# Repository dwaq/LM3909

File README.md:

# LM3909
A clone of National Semiconductor's LM3909 IC using discrete components on a PCB.

Project page: [https://hackaday.io/project/29179-disintegrated-lm3909-15v-led-flasher](https://hackaday.io/project/29179-disintegrated-lm3909-15v-led-flasher)

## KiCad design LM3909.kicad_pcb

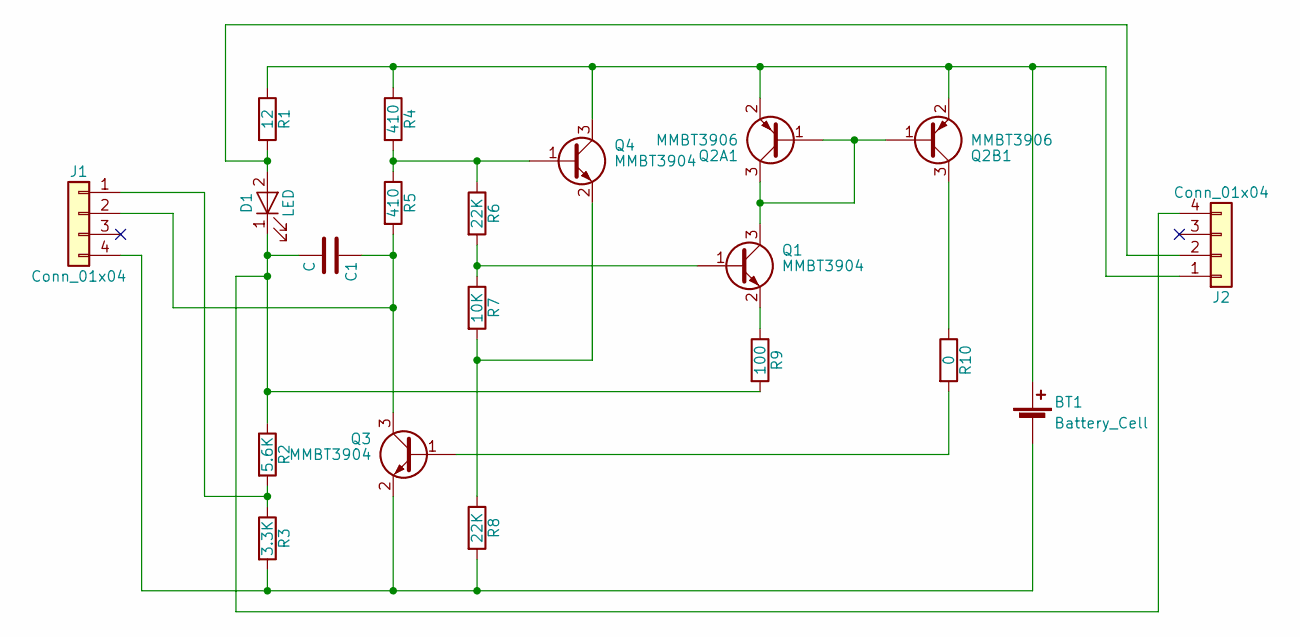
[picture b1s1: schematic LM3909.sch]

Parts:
BT1: Battery_Cell
C1: C; C_1206
D1: LED; LED_0805
J1, J2: Conn_01x04; Pin_Header_Straight_1x04_Pitch2.54mm
Q1, Q3, Q4: MMBT3904; SOT-23
Q2A1, Q2B1: MMBT3906; SOT-23
R1: 12; R_0805
R2: 5.6K; R_0805
R3: 3.3K; R_0805
R4, R5: 410; R_0805
R6, R8: 22K; R_0805
R7: 10K; R_0805
R9: 100; R_0805
R10: 0; R_0805

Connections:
unnamed 0: BT1.1 (+), J2.1, Q2A1.2 (E), Q2B1.2 (E), Q4.3 (C), R1.1, R4.1; also elsewhere on the board
unnamed: BT1.2 (-), J1.4, Q3.2 (E), R3.2, R8.2
unnamed: C1.1, J1.2, Q3.3 (C), R5.2
unnamed: C1.2, D1.1 (K), J2.4, R2.1, R9.2
unnamed: D1.2 (A), J2.2, R1.2
unnamed: J1.1, R2.2, R3.1
unnamed: Q1.1 (B), R6.2, R7.1
unnamed: Q1.2 (E), R9.1
unnamed 10: Q1.3 (C), Q2A1.1 (B), Q2A1.3 (C), Q2B1.1 (B); also elsewhere on the board
unnamed: Q2B1.3 (C), R10.1
unnamed: Q3.1 (B), R10.2
unnamed: Q4.1 (B), R4.2, R5.1, R6.1
unnamed: Q4.2 (E), R7.2, R8.1

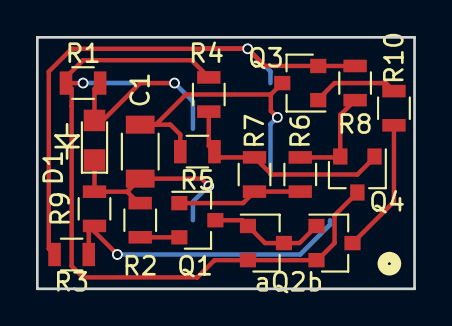
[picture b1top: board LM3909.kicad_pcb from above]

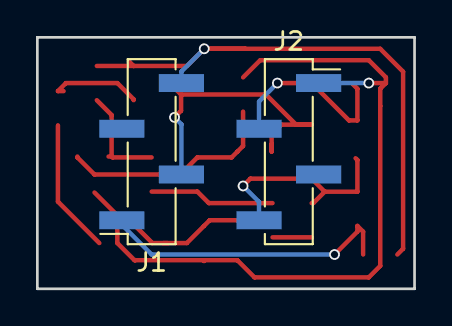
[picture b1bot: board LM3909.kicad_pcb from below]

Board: 2 copper layers, 21.0 x 14.0 mm, 19 parts (2 on the bottom side), 13 nets.

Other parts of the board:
aQ2b: MMBT3906; SOT-23

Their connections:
unnamed 0: aQ2b.2; also elsewhere on the board
unnamed 10: aQ2b.1, aQ2b.3; also elsewhere on the board

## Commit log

2017-11-29 init kicad project
2017-11-29 add gitignore
2017-11-29 connect all components in schematic
2017-11-29 add values
2017-11-29 add reference designators
2017-11-29 add 0805 footprints to many components
2017-11-29 generate netlist
    and automatically rename Q2x to Q2x1
2017-11-29 ignore other files
2017-11-29 place components on PCB
2017-11-29 start to lay traces
2017-11-30 replace through hole transistors with smd parts
2017-11-30 add another R that can be used intead of transistor current mirror
2017-11-30 route some more
2017-12-01 connected everything on one layer
2017-12-01 condensed
2017-12-01 much smaller
2017-12-01 loop wires other way
2017-12-01 pretty dang small
2017-12-01 condense schematic
2017-12-01 add pins to schematic
2017-12-01 add through hole pin footprint
2017-12-03 new footprint
    switched to offset smd
    in correct position to match DIP
2017-12-04 replace BC8*7 with MMBT390* transistors
2017-12-04 hide text on board
    Visables -> Render -> Text Front & Text Back
2017-12-04 connect the 6 pins on the bottom layer
2017-12-06 add board outline
2017-12-06 move silkscreen into place
2017-12-06 move components and add pin 1 marker
2017-12-06 ignore gerbers (for now)
2017-12-06 display better
2017-12-06 add LED symbol
2017-12-06 move text a little
2017-12-11 mark 2 pins as no connect
2017-12-11 increase cap footprint to 0805
2017-12-11 change resistors from 410 to 510 ohm
2018-01-03 Add Gerbers from manufactured design
2018-01-03 add description and project page link
